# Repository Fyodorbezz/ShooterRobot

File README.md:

# Shooter robot
2 Axis gimbling platform with machine vision that recognizes objects on the wall and points laser to them. Created for robotics Olympiad. 

YouTube link: https://www.youtube.com/watch?v=qjWNKVldk8c

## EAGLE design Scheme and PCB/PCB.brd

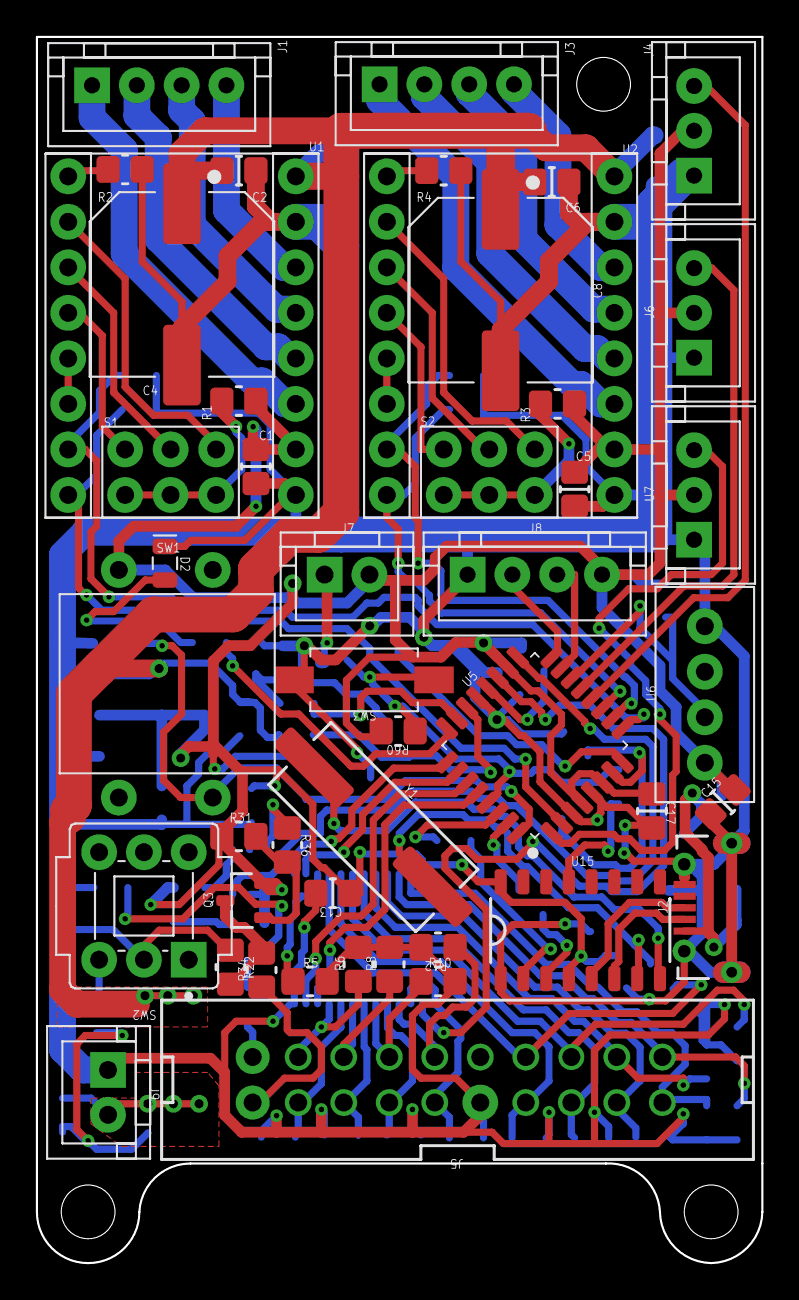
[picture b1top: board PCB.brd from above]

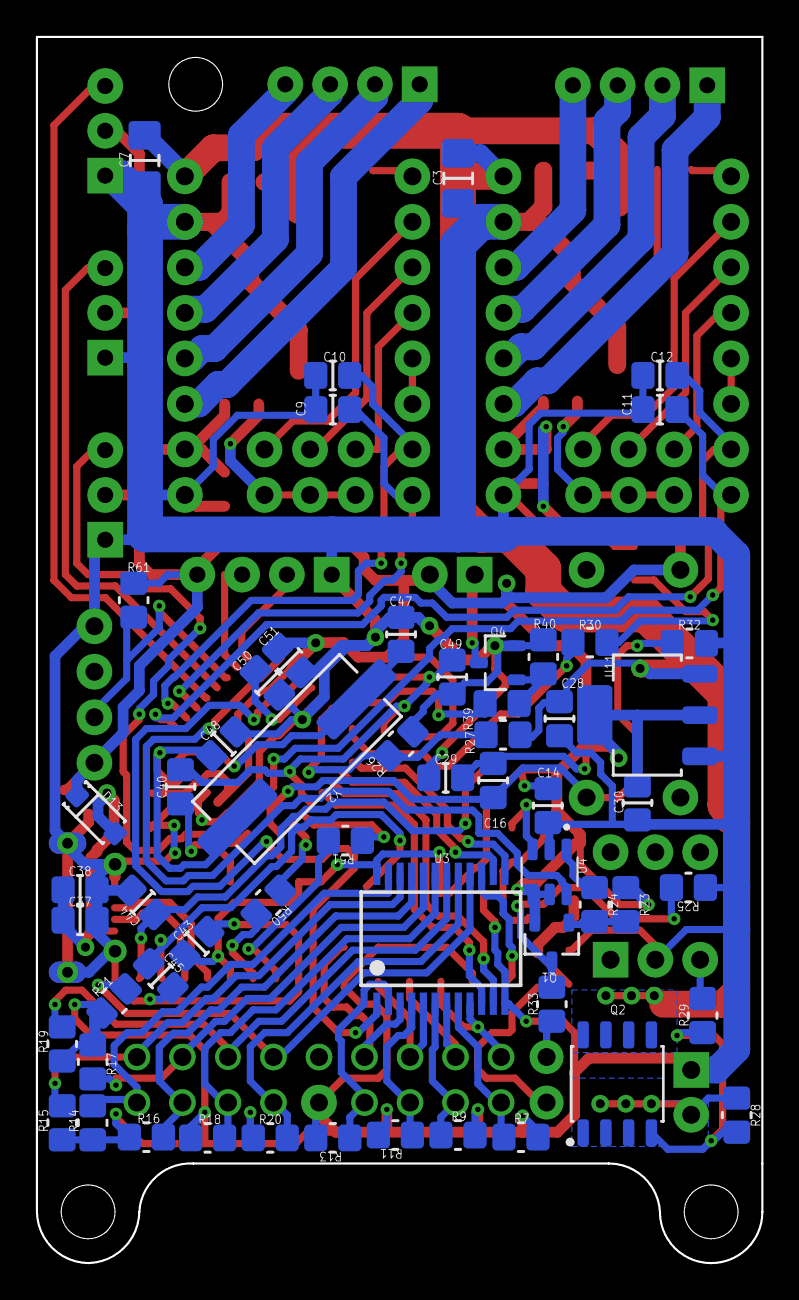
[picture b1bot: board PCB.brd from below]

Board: 2 copper layers, 40.5 x 68.4 mm, 103 parts (57 on the bottom side), 88 nets.

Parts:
C1, C5: 100nF; Cap
C2, C6: 100nF; Cap_C2
C3, C7: 10uF; CAP_1206
C4: 1000uF; CAPAE-10.3x10.3h13.5
C8: 1000uF; CAPAE-10.3x10.3h13.5_C8
C9, C11, C49: 10nF; Cap_C9
C10, C12: 10nF; Cap_C10
C13, C15, C17: 100nF; Cap_C13
C14: 100nF; Cap_C9
C16: 10nF; Cap_C16
C28: 10uF; Cap_C28
C29: 10uF; Cap_C29
C30: 10uF; Cap_C10
C37, C40, C43: 100nF; Cap_C29
C38: 1uF; Cap_C29
C44, C45, C48: 22pF; Cap_C29
C47: 22pF; Cap_C9
C50, C51: 100nF; Cap_C50
D2: Yellow; LED_0805(2012_Metric)_N_Red
D13: DIO; Diode
J1, J3: STEP_MOT; B4B-XH-A
J2: USB; JEEC_920-E52A2021S10100
J4: ENDSTOP; B3B-XH-A
J5: SENSOR; IDC20M
J6: ENDSTOP; B3B-XH-A_J6
J7: LASER; B2B-XH-A
J8: ULTRASONIC; B4B-XH-A_J8
J9: POWER; B2B-XH-A
Q1: P MOSPFET; SOT23-3P95_230X110L30X43N
Q2: IRF4905LPBF; SOIC8P127_488X585X363L48X40M
Q3: P MOSPFET; SOT23-3P95_230X110L30X43N_Q3
Q4: N MOSPFET; SOT23-3P95_230X110L30X43N_Q4
R1, R3: 1K; Res
R2, R4: 10K; Res_R2
R5, R6, R8, R10, R12, R22, R31, R60: 10K; Res_R5
R7, R9, R11, R13, R14, R15, R16, R17, R18, R19, R20, R21, R23, R25, R28: 10K; Res_R7
R24, R29, R33: 100R; Res_R7
R26, R40: 10K; Res_R26
R27: 8K; Res_R27
R30: 100R; Res_R30
R32: 10K; Res_R30
R34, R36: 100R; Res_R5
R39: 100R; Res_R39
R50, R51: 1K; Res_R7
R61: 47K; Res_R61
S1, S2: 3XSWITCH; Untitled
SW1: ON BUTTN; button
SW2: POWER SWITCH; CK_PVA2-H1
SW3: RES BTN; RES_btn
U1, U2: DRIVER; Untitled_U1
U3: 1:16 MLTIPLECSOR; SSOP24
U4: 1:2 MULTIPLECSOR; SOT95P280X145-6N
U5: ATMEGA328P; QFP32P80_900X900X120L60X37L_AD2
U6: DHT; DHT22
U7: SERVO; B3B-XH-A_J6
U11: AMS1117-3.3; SOT223-4P230_700X180L100X70N_AD1
U15: CH340G; SOIC16P127_1000X600X180L50X45N
Y1: 12MHz; XTAL1140X490X430D1340L450X60N
Y2: 16MHz; XTAL1140X490X430D1340L450X60N_Y2

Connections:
Gnd: C1.2, C2.1, C3.1, C4.2, C5.2, C6.1, C7.1, C8.2, C9.2, C10.2, C11.2, C12.2, C13.2, C14.1, C15.1, C17.2, C28.1, C29.1, C30.2, C37.2, C38.2, C43.2, C44.2, C45.2, C47.2, C48.2, C49.1, C50.2, C51.2, D2.1, J2.5, J2.6@, J2.6@_1, J2.6@_2, J2.6@_3, J4.1, J5.11, J6.1, J8.1, J9.1, Q4.2, R2.1, R4.1, R5.2, R6.2, R7.2, R8.2, R9.2, R10.2, R11.2, R12.2, R13.2, R14.1, R15.1, R16.1, R17.1, R18.1, R19.1, R20.1, R21.1, R22.1, R25.1, R26.1, R32.1, R40.2, SW2.2, SW3.2, U1.9, U1.15, U2.9, U2.15, U3.12, U4.2, U5.3, U5.5, U5.21, U6.4, U7.1, U11.1, U15.1
Net_0: Q4.1, R39.2, R40.1
Net_1: R24.1, U4.1
Net_2: C2.2, C3.2, C4.1, C6.2, C7.2, C8.1, C28.2, Q2.5, Q2.6, Q2.7, Q2.8, R27.1, U1.16, U2.16, U11.3
Net_3: U1.5, U1.6
Net_4: U2.5, U2.6
Net_5: J3.4, U2.14
Net_6: J3.3, U2.13
Net_7: J3.2, U2.12
Net_8: J3.1, U2.11
Net_9: J5.10, R12.1, U3.3
Net_10: J5.2, R33.1
Net_11: Q3.3, R22.2, R34.2
Net_12: R3.2, S2.1, S2.2, S2.3
Net_13: R4.2, U2.1
Net_14: Q3.1, R31.2, R36.2
Net_15: R36.1, U4.3
Net_16: J8.2, U5.16
Net_17: Q1.1, R23.2, R24.2
Net_18: R26.2, R27.2, U5.22
Net_19: J1.4, U1.14
Net_20: J1.3, U1.13
Net_21: J1.2, U1.12
Net_22: J1.1, U1.11
Net_23: S1.6, U1.2
Net_24: S1.5, U1.3
Net_25: S1.4, U1.4
Net_26: R1.2, S1.1, S1.2, S1.3
Net_27: R2.2, U1.1
Net_28: C12.1, U1.7, U5.9
Net_29: C11.1, U1.8, U5.2
Net_30: C10.1, U2.7, U5.10
Net_31: J9.2, Q2.1, Q2.2, Q2.3, R28.1
Net_32: R29.2, SW2.3
Net_33: Q2.4, R28.2, R29.1
Net_36: S2.4, U2.4
Net_37: S2.5, U2.3
Net_38: S2.6, U2.2
Net_41: C9.1, U2.8, U5.11
Net_42: J4.3, U5.12
Net_43: J6.3, U5.13
Net_44: U3.1, U5.19
Net_45: U3.10, U5.28
Net_46: U3.11, U5.27
Net_47: U3.14, U5.26
Net_48: U3.13, U5.25
Net_49: R5.1, U3.15
Net_50: J5.1, R34.1
Net_51: J5.9, R13.1, U3.2
Net_52: Q1.3, R25.2, R33.2
Net_53: J5.7, R11.1, U3.4
Net_54: J5.8, R10.1, U3.5
Net_55: J5.5, R9.1, U3.6
Net_56: J5.6, R8.1, U3.7
Net_57: J5.3, R7.1, U3.8
Net_58: J5.4, R6.1, U3.9
Net_59: J5.19, R14.2, U3.23
Net_60: J5.20, R15.2, U3.22
Net_61: J5.17, R16.2, U3.21
Net_62: J5.18, R17.2, U3.20
Net_63: J5.15, R18.2, U3.19
Net_64: J5.16, R19.2, U3.18
Net_65: J5.13, R20.2, U3.17
Net_66: J5.14, R21.2, U3.16
Net_67: U4.6, U5.17
Net_68: J7.1, Q4.3
Net_69: R50.1, U5.31
Net_70: R39.1, U5.23
Net_72: R51.2, U15.2
Net_73: R50.2, U15.3
Net_74: C40.1, U15.13
Net_75: J8.3, U5.15
Net_76: J2.3, U15.5
Net_77: J2.2, U15.6
Net_78: C37.1, C38.1, D13.2, J2.1
Net_82: R30.2, U5.24
Net_83: D2.2, R30.1
Net_85: C16.2, R32.2, SW1.4, U5.32
Net_86: U5.1, U7.3
Net_87: C40.2, C49.2, R60.1, SW3.1, U5.29
Net_97: C48.1, U5.7, Y2.2
Net_100: C50.1, U5.20
Net_105: R51.1, U5.30
Net_110: C44.1, U15.8, Y1.1
Net_111: C45.1, U15.7, Y1.2
Net_125: R61.2, U5.14, U6.2
Net_155: C47.1, U5.8, Y2.1
USBVCC: C1.1, C5.1, C13.1, C14.2, C15.2, C16.1, C17.1, C29.2, C30.1, C43.1, C51.1, D13.1, J4.2, J6.2, J7.2, J8.4, Q1.2, Q3.2, R1.1, R3.1, R23.1, R31.1, R60.2, R61.1, SW1.1, U1.10, U2.10, U3.24, U4.4, U4.5, U5.4, U5.6, U5.18, U6.1, U7.2, U11.2, U11.4, U15.4, U15.16

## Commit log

2024-02-07 Add scheme and pcb
2024-02-07 Add all matereals
2024-02-07 Add PCB and scheme with different format
2024-08-27 Added preview
2024-08-27 Updated preview
2024-08-27 Create LICENSE
